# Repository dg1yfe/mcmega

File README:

MCmega is a port of the MC70 firmware to the AVR platform.
It provides an alternative firmware for Motorola MC micro transceivers to enable the use of those radios for HAM radio.
The project includes a PCB (printed ciruit board) with an ATMega64 which is designed to replace the original CPU on the GLN6628B/GLN6984A command board used in the MC micro model EZA9.

Check out the details on the projects homepage:
http://mc70.stus-disco.de

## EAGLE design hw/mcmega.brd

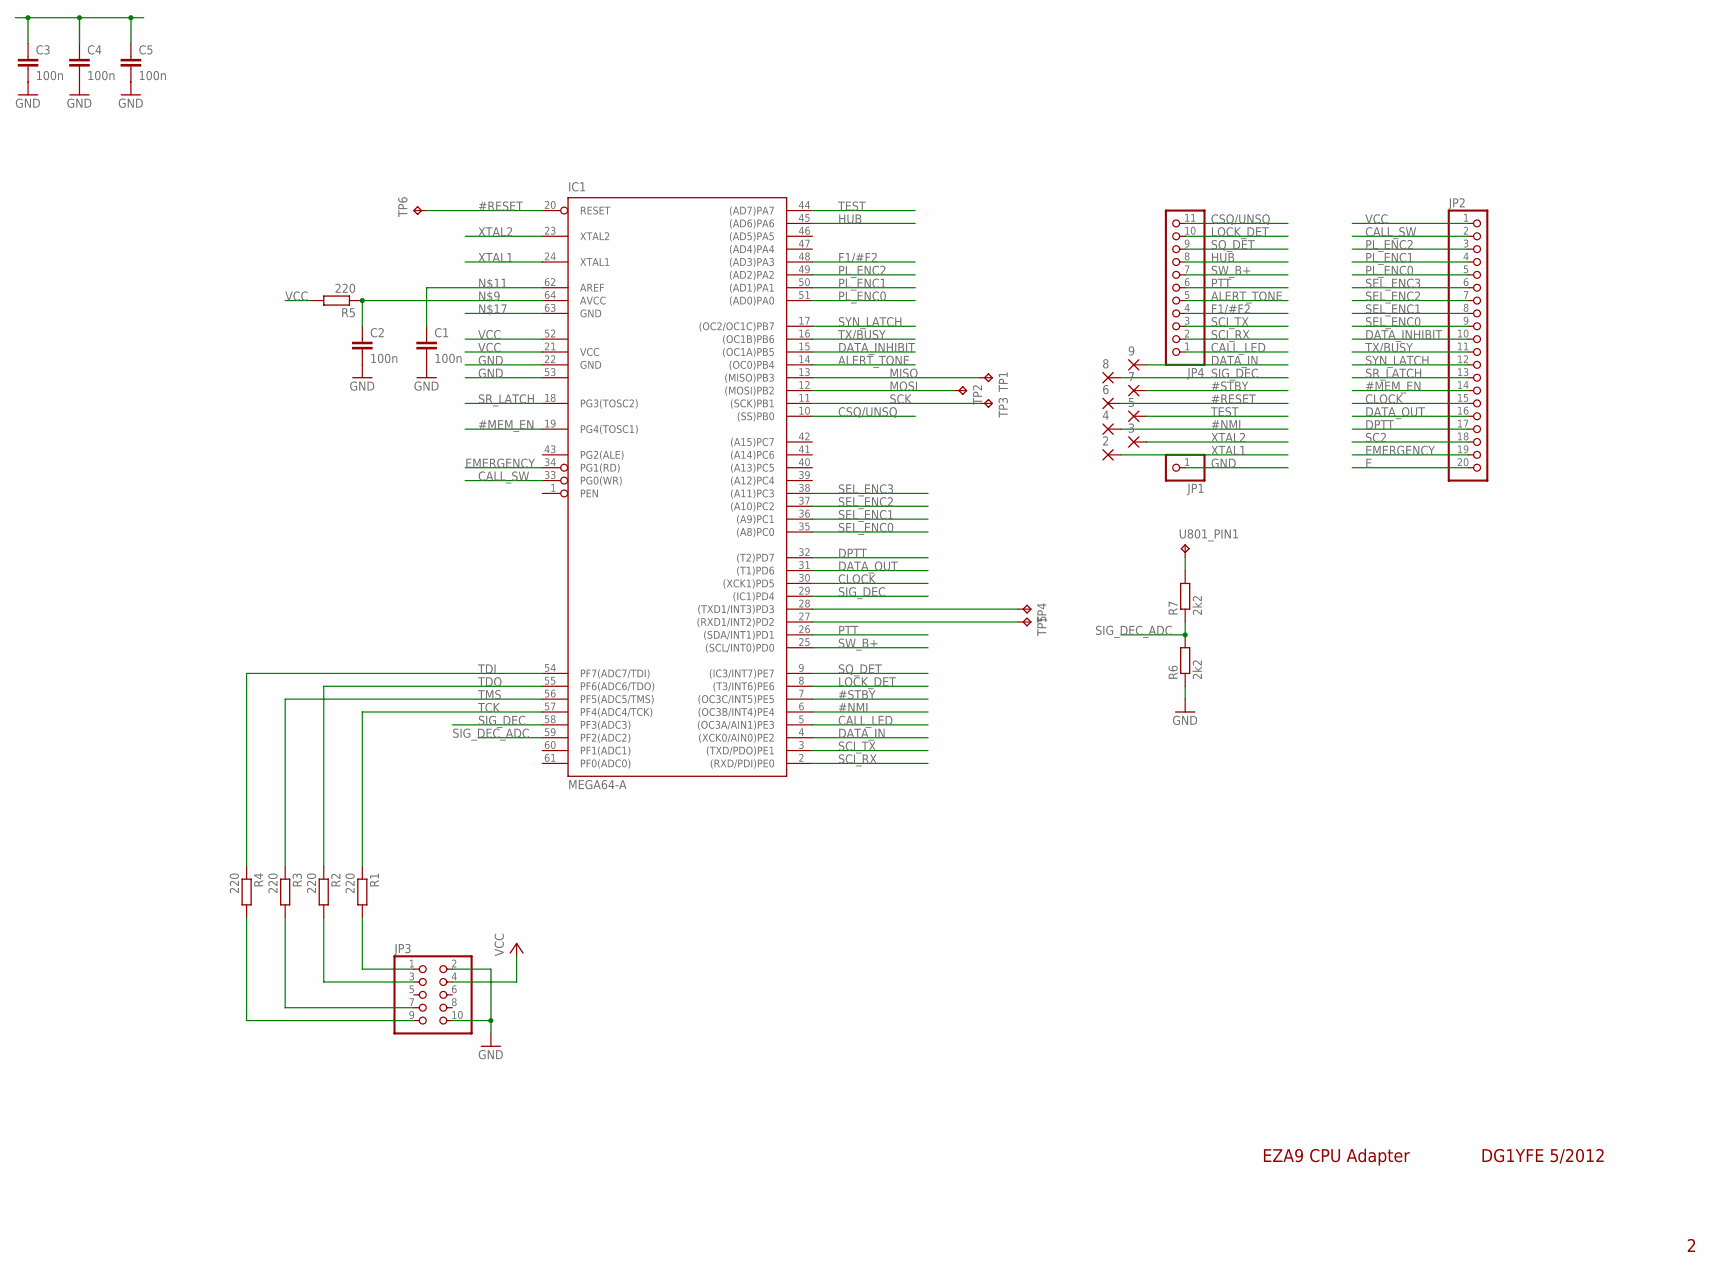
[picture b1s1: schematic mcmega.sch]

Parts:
2, 3, 4, 5, 6, 7, 8, 9: SMD2; SMD1,27-2,54
C1, C2, C3, C4, C5: 100n; C0603
IC1: MEGA64-A; TQFP64
JP1: PINHD-1X1; 1X01
JP2: PINHD-1X20; 1X20
JP3: PINHD-2X5; 2X05
JP4: PINHD-1X11; 1X11
R1, R2, R3, R4, R5: 220; R0603
R6, R7: 2k2; R0603
TP1, TP2, TP3, TP4, TP5, TP6: TPTP09R; TP09R
U801_PIN1: TPTP10R; TP10R

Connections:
#MEM_EN: IC1.19 (PG4(TOSC1)), JP2.14
#NMI: 4.1, IC1.6 ((OC3B/INT4)PE4)
#RESET: 6.1, IC1.20 (RESET), TP6.TP
#STBY: 7.1, IC1.7 ((OC3C/INT5)PE5)
ALERT_TONE: IC1.14 ((OC0)PB4), JP4.5
CALL_LED: IC1.5 ((OC3A/AIN1)PE3), JP4.1
CALL_SW: IC1.33 (PG0(WR)), JP2.2
CLOCK: IC1.30 ((XCK1)PD5), JP2.15
CSQ/UNSQ: IC1.10 ((SS)PB0), JP4.11
DATA_IN: 9.1, IC1.4 ((XCK0/AIN0)PE2)
DATA_INHIBIT: IC1.15 ((OC1A)PB5), JP2.10
DATA_OUT: IC1.31 ((T1)PD6), JP2.16
DPTT: IC1.32 ((T2)PD7), JP2.17
E: JP2.20
EMERGENCY: IC1.34 (PG1(RD)), JP2.19
F1/#F2: IC1.48 ((AD3)PA3), JP4.4
GND: C1.2, C2.2, C3.2, C4.2, C5.2, IC1.22 (GND), IC1.53 (GND1), JP1.1, JP3.2, JP3.10, R6.1
HUB: IC1.45 ((AD6)PA6), JP4.8
LOCK_DET: IC1.8 ((T3/INT6)PE6), JP4.10
MISO: IC1.13 ((MISO)PB3), TP1.TP
MOSI: IC1.12 ((MOSI)PB2), TP2.TP
unnamed: JP3.1, R1.2
unnamed: JP3.3, R2.2
unnamed: JP3.7, R3.2
unnamed: JP3.9, R4.2
unnamed: R7.2, U801_PIN1.TP
unnamed: C2.1, IC1.64 (AVCC), R5.1
unnamed: C1.1, IC1.62 (AREF)
unnamed: IC1.28 ((TXD1/INT3)PD3), TP4.TP
unnamed: IC1.27 ((RXD1/INT2)PD2), TP5.TP
PL_ENC0: IC1.51 ((AD0)PA0), JP2.5
PL_ENC1: IC1.50 ((AD1)PA1), JP2.4
PL_ENC2: IC1.49 ((AD2)PA2), JP2.3
PTT: IC1.26 ((SDA/INT1)PD1), JP4.6
SC2: JP2.18
SCI_RX: IC1.2 ((RXD/PDI)PE0), JP4.2
SCI_TX: IC1.3 ((TXD/PDO)PE1), JP4.3
SCK: IC1.11 ((SCK)PB1), TP3.TP
SEL_ENC0: IC1.35 ((A8)PC0), JP2.9
SEL_ENC1: IC1.36 ((A9)PC1), JP2.8
SEL_ENC2: IC1.37 ((A10)PC2), JP2.7
SEL_ENC3: IC1.38 ((A11)PC3), JP2.6
SIG_DEC: 8.1, IC1.29 ((IC1)PD4), IC1.58 (PF3(ADC3))
SIG_DEC_ADC: IC1.59 (PF2(ADC2)), R6.2, R7.1
SQ_DET: IC1.9 ((IC3/INT7)PE7), JP4.9
SR_LATCH: IC1.18 (PG3(TOSC2)), JP2.13
SW_B+: IC1.25 ((SCL/INT0)PD0), JP4.7
SYN_LATCH: IC1.17 ((OC2/OC1C)PB7), JP2.12
TCK: IC1.57 (PF4(ADC4/TCK)), R1.1
TDI: IC1.54 (PF7(ADC7/TDI)), R4.1
TDO: IC1.55 (PF6(ADC6/TDO)), R2.1
TEST: 5.1, IC1.44 ((AD7)PA7)
TMS: IC1.56 (PF5(ADC5/TMS)), R3.1
TX/BUSY: IC1.16 ((OC1B)PB6), JP2.11
VCC: C3.1, C4.1, C5.1, IC1.21 (VCC), IC1.52 (VCC1), JP2.1, JP3.4, R5.2
XTAL1: 2.1, IC1.24 (XTAL1)
XTAL2: 3.1, IC1.23 (XTAL2)

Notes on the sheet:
EZA9 CPU Adapter
DG1YFE 5/2012

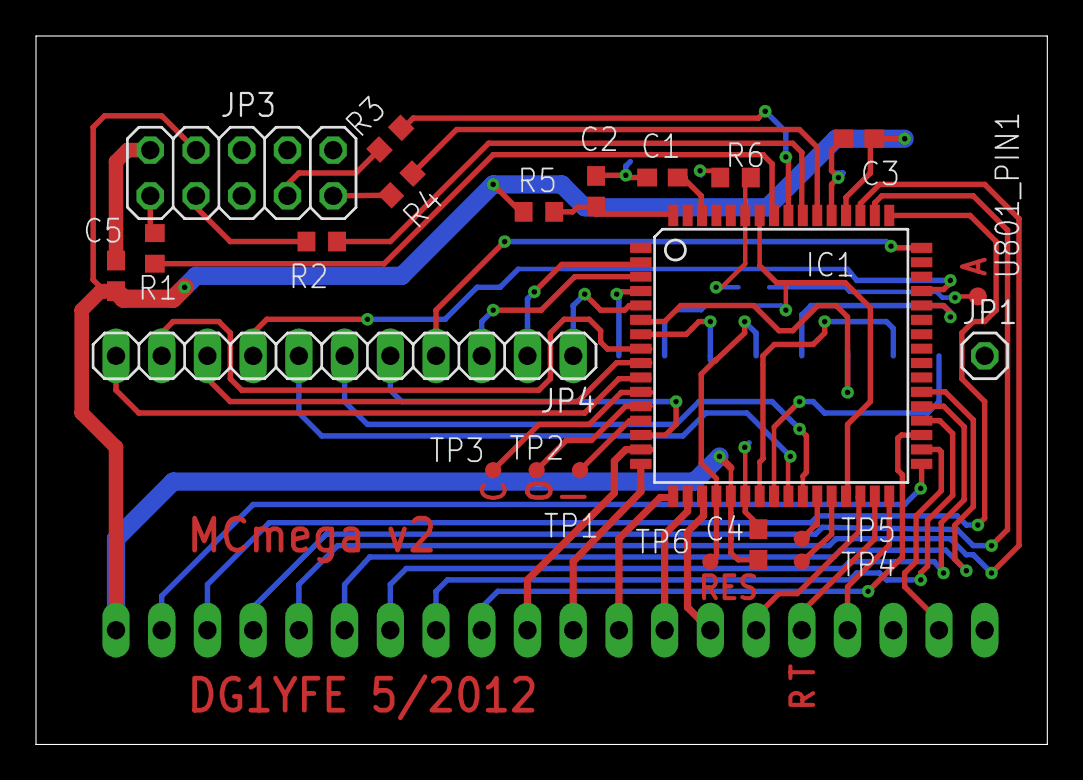
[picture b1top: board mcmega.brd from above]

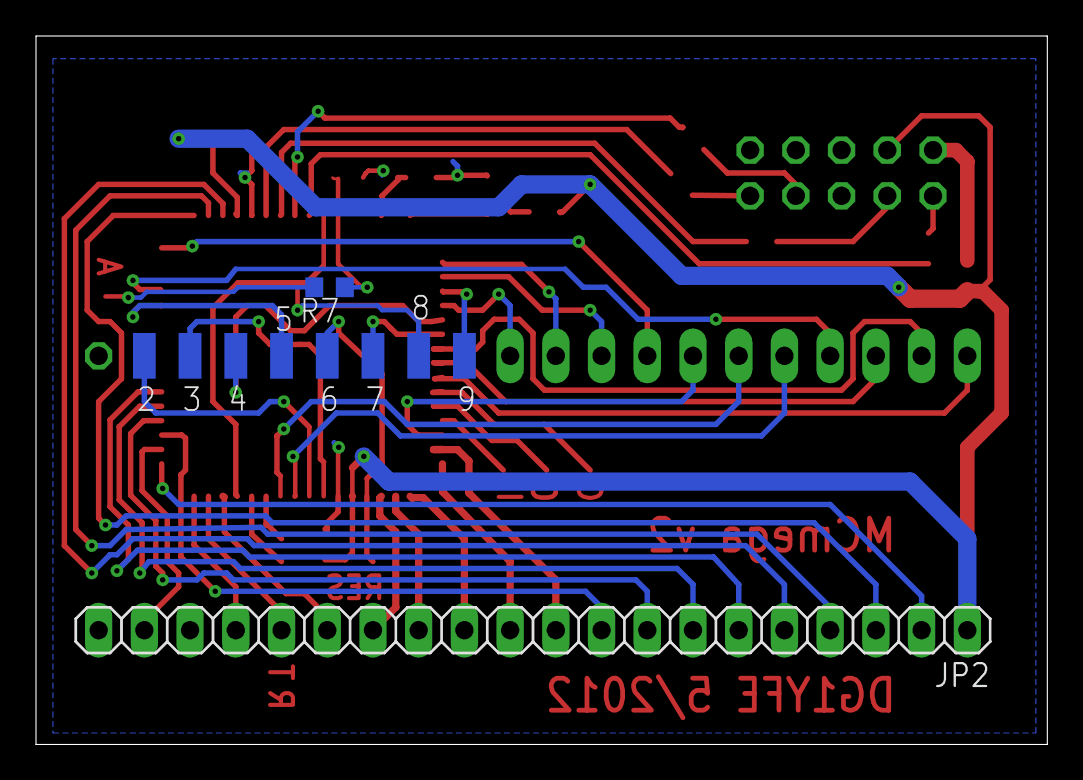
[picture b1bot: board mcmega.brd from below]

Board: 2 copper layers, 56.2 x 39.4 mm, 32 parts (10 on the bottom side), 55 nets.

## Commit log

2012-05-27 Initial commit, started to port ASM code to C
2012-05-28 Ported io.asm
2012-05-28 Ported pll_freq and display, began work on menu
2012-06-16 Continued to port menu, re-implemented sci rx/tx & ack, introduced sci tx/rx handler in control task (replacing sci irq handler)
2012-06-17 more work on menus
2012-07-10 Added menu_mem
2012-07-12 Ported subs.c
2012-07-12 timer.c / math.c, some fixes, some extensions
2012-07-13 Implemented / ported most of EEPROM.asm
2012-07-13 Compiles for the first time ... needs bugfixing!
2012-07-15 Included menu_mem.h Header file
2012-07-15 fixed includes switched to avr-gcc 4.5.1, changed code to compile (removed inline stuff for now, etc...)
2012-07-17 Some Bugfixes, changes for debugging
2012-07-17 Put HW files in HW folder
2012-07-17 Updated HW files
2012-07-18 Implemented Queues for RX processing, set clock macro to 8 MHz
2012-07-18 Bugfix regarding UART rx, debugging LCD Reset & Comm
2012-07-19 Further changes to comm handling, control head comm still broken
2012-07-19 More work on comm, needs testing
2012-07-20 more work on comm, still broken
2012-07-20 Possibly fixed tx comm issue, needs testing
2012-07-20 Fixed bugs related to comm, key input and LED setting
2012-07-20 Bugfix in eep_seq_read(), fixed deadlock
2012-07-20 Bugfix in Arrow_set (arrow on was not working properly), changed/improved lcd reset
2012-07-20 Implemented freq_init(), bugfix in pll_set_channel(), improved comm handling (regarding successive keypresses), etc...
2012-07-21 Tried to improve control head reset
2012-07-21 Implemented display/control head reset & reinitialization during operation (e.g. CH was powered down without resetting radio)
2012-07-21 Bugfix: PLL lock state was not displayed
2012-07-22 Fixed serial bus access (timing, signal integrity), bugfix in set_pll() (did not set correct divider)
2012-07-22 Bugfix: SWB check tested 'PORT' instead of 'PIN'
2012-07-22 Included experimental support for audio pa soft on/off
2012-07-22 Fixed UI related bugs (frequency & shift input, output functions, etc.), Improved lcd_fill: Only restore cpos, if cpos changed
2012-07-22 Bugfix: PTT was not read correctly, Bugfix: TX frequency was not set correct (division result was not used)
2012-07-22 Bugfix in lcd comm (0x4c / 0x5c were recognized as extended char), Bugfixes for menu/submenu function calls, Bugfixes for I2C comm., Implemented rfpwr_set() & rfpwr_print() and macro for default rf p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
2012-07-23 Bugfixes regarding recall & store menu and EEPROM comm.
2012-07-24 Bugfix in EEPROM access, included support for internal EEPROM, TODO: Implement function to transfer original channel data from ext. EEPROM to internal EEPROM
2012-07-24 Menu improvements, include write_current & show_version
2012-07-24 Began to implement audio support
2012-07-25 Implemented audio functionality, requires testing!
2012-07-26 Bugfixes in Audio output, CTCSS TX and 1750 Hz now working, added calibration submenu to tune internal RC Oscillator (required for CTCSS to work)
2012-07-31 Included tone decoding, Included HW reset of control head
2012-07-31 CTCSS Tone decoding works (minor HW change necessary, 1k parallel to R837 (1k2)), implemented rudimentary CTCSS squelch (carrier AND tone))
2012-08-01 Included optimized inline asm for multiplication in Goertzel routines, began to include config specific code
2012-08-01 Included 270 Hz IIR lowpass
2012-08-03 Bugfixes & optimizations for tone decoding
2012-08-03 enable CTCSS rx by default for tests
2012-08-05 rewrote goertzel_process() using inline asm for increased resolution
2012-08-05 Some bugifxes in audio processing
2013-02-27 Implement goertzel using floating point, use CIC decimation to reduce sample-rate, use chebychev low-pass for amplitude correction (WORK IN PROGRESS)
2013-03-01 Small changes, make code compile using latest AVR Toolchain for win
2013-03-03 Tone detection works, speed-up in main-loop - only yield if sample buffer is nearly empty, test-code still in place
2013-04-28 Goertzel output is now relative to block length, more debug output
2013-04-28 Include extra input and voltage divider for connection U801/Pin1 to ADC (enhanced signal detection)
2013-04-29 Use ADC for tone detection, reset tone decoder on squelch pin rising edge
2013-11-10 Include / update license info, implement config structure and eep_rd_memcd
2013-11-10 Include Copying (GPL v3 info) and README
2013-11-18 Bugfix: Enable watchdog, select correct bit to toggle. Enable yellow LED on RX (Busy LED)
2013-11-18 Bugfix: Use correct key (*) to change sign of tx shift
2013-11-18 Bugfix: TX shift input was not properly terminated
2013-11-18 Remove fix setting of OSCCAL (TODO: Perform proper read-out of calibration data / perform proper calibration / Use external Xtal oscillator, update version info, put version info in one place
2014-03-17 Some fixes regarding shift settings
2014-03-18 Included MC Mega Bootloader as submodule
2014-04-28 Bugfix: Disable yellow LED when squelch is closed
2014-04-28 Bugfix: Limit PLL datarate: PLL was not properly programmed when compiled with optimizations activated due to rise-time & fall-time violations
2014-04-28 Make warning about exceeded OCR2 more informative (state reason)
2014-04-28 Bugfix: Disable yellow LED when NOT receiving or transmitting (now for real ;) )
2014-04-28 Change frequency related variable type from unsigned long to uint32_t
2014-04-28 Combine multiple config variables into one struct, Introduce 'same as rx' / 'same as tx' for CTCSS frequency selection, include CTCSS frequencies into config struct
2014-04-29 Updated bootloader submodule
2014-04-29 Little bugfix
2014-05-01 Put configuration stuff in one place, save it to EEPROM and restore it (work in progress)
2014-05-01 Reduce block time in sci_tx, ignore calls to set shift register originating from UI task
2014-05-01 Optimize samplerate for 4.9 MHz, do not use chebychev filter for CIC roll-off compensation to save CPU time
2014-05-01 Define INCLUDE_xTaskGetCurrentTaskHandle to be able to determine the currently running task
2014-05-01 Implement new config handling, remove shared-variable data passing between UI and control task
2014-05-01 Updated to latest bootloader code
2014-05-01 Bugfix: remove infinite loop in config crc check
2014-05-01 Bugfixes related to new config scheme (fix CRC calculation, fix passing of squelch & power cfg, fix frequency input handling)
2014-05-02 Updates & fixes to config handling. There is only one config structure, UI task is only allowed to read, Updates come as messages
2014-05-02 Apply configuration on (re-)boot
2014-05-04 Bugfixes & cleanup regarding configuration, update EEPROM config only if it differs from SRAM, initialize squelch from config and no longer in menu_init()
2014-05-04 Feature: Add direct DTMF output during tx for buttons 0-9, * and #
2014-05-04 Rename default channel save to config save
2014-05-11 Debugging audio out, optimized audio ISR
2014-08-01 Include GetShiftReg()
2015-07-28 Picked some changes from mucploepp branch
2015-10-11 Began autocal - calibrate internal RC oscillator using the contrl heads data signal
2015-10-31 Erster Entwurf für Autocal
2016-09-07 Updated mcmboot URL to point to github, updated to latest bootloader (mcmboot) commit
2016-09-07 Began faster float add & mul
2016-09-07 Rename MATH_H_ to MCM_MATH_H_ and include fast float prototypes
2017-02-13 Use fastfloat for tone detection
2017-02-15 Updates to use new tone decoder, include log10 with fastfloat
